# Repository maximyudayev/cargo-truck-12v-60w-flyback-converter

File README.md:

# Heavy-Duty Truck 12V 60W Flyback DC/DC Converter
18V-32V input 12V output, 60W (5A) nominal 84W (7A) maximum, 60mm-by-30mm-by-25mm, no-opto flyback DC/DC converter with synchronous secondary rectifier, up to 97% efficiency, excellent static and dynamic output regulation for heavy-duty truck applications like interior appliances, ADAS, lighting, supplies for consumer electronics, etc.

Below is the efficiency and duty cycle graph as a function of load:

This DC/DC converter was built as part of my Power Electronics course at KU Leuven - Campus GroupT in academic year 2020-2021, taught by the awesome duo of Gert and Gorik :wink:

The converter was designed, built and tested. Results of the test can be found in the final report of the course, which also includes all the detailed calculation steps and side-by-side comparison to a synchronous buck converter designed and built by my lab partner Matthias.

## Features
- [X] Clean, readable and well-documented
- [X] Operating range of normal battery voltages
- [X] <500mV input/output ripple
- [X] Low-cost prototype
- [X] Dual-variant primary clamp
- [X] Dual-variant secondary rectifier
- [ ] TVS circuit on the input
- [ ] Multiple output rails (5V, 3V3)
- [ ] Dynamic load ripple under 50-100mV
- [ ] Heat management #1

PCB front side:

PCB back side:

All the design files are under GPL3 and can be freely used for personal projects where this device can be of use.

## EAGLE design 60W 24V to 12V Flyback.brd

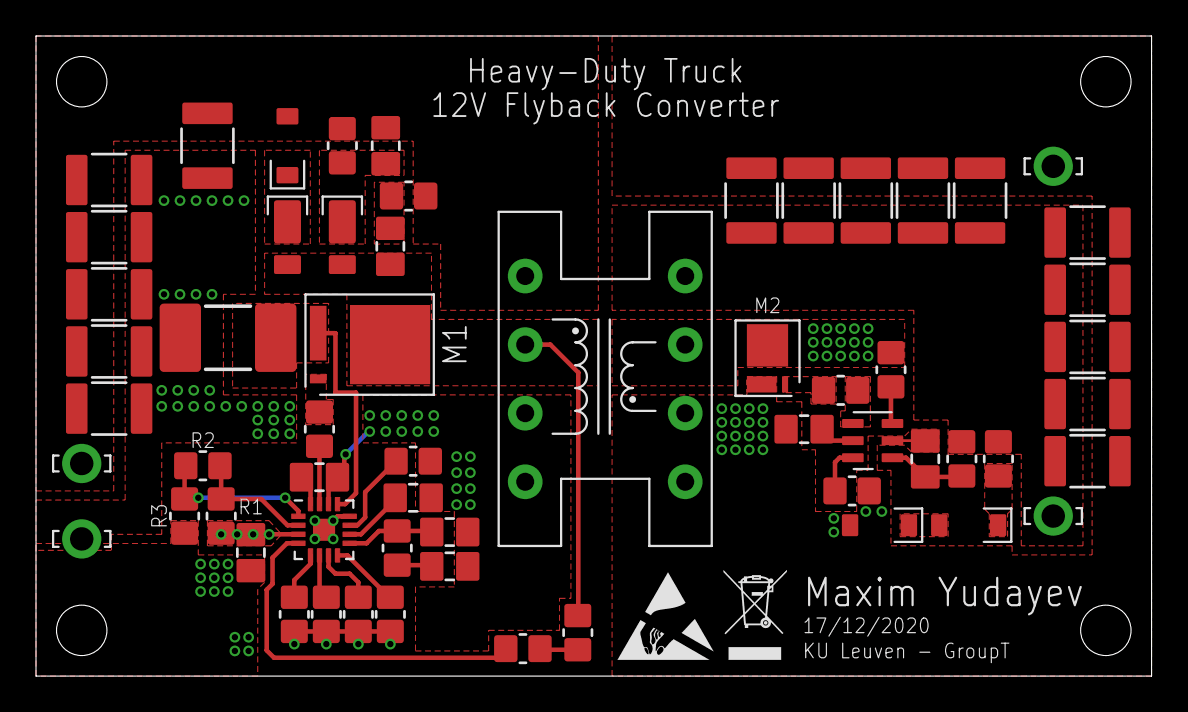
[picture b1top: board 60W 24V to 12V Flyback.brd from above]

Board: 2 copper layers, 62.0 x 35.6 mm, 60 parts (1 on the bottom side), 33 nets.

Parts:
+12V, +24V: TAB_37800568(MSTIN); HOLE_1-3
C1, C2, C3, C4, C5, C6, C7, C8, C9, C10: 22u; C1210K
C11, C12, C13, C14, C15, C16: 10u; C1210K
C17, C18, C19, C23: 4u7; C0805K
C20, C22: 47n; C0805K
C21: 560p; C0805K
C24: 220p; C0805K
C25: 150n; C0805K
CHASSIS: TAB_37800568(MSTIN); HOLE_1-3
D1, D3: DFLS2100-7; DFLS2100_DS31475
D2: MMSZ5270BT1G; MMSZ?T1G_SOD-123_425-04
D4, D5: MMSZ4692T1G; MMSZ?T1G_SOD-123_425-04
D6: B540C-13-F; B5?0C-13-F_DO-214AB_DS13012
GND: TAB_37800568(MSTIN); HOLE_1-3
M1: BSC096N10LS5; BSC096N10LS5_TDSON-8
M2: BSZ039N06NS; BSZ039N06NS_TSDSON-8_Z8B00158553
R1: 228k; R0805
R2: 3k83; R0805
R3, R4: 10k; R0805
R5: 6k49; R0805
R6: 22; R0805
R7: 147k; R0805
R8: 5m; R2512
R9: 3k6; R0805
R10: 33k2; R0805
R11: 137k; R0805
R12: 124k; R0805
R13: R0805
R14: 357; R0805
R15, R16: 1R2; R0805
R17: 220k; R0805
R18: 47; R0805
R19: 10k2; R0805
R20: 5R1; R0805
T1: TRANS_EPCOS_8; TRANS_EPCOS-B66307_E16/8/5_0.5_3.45UH_200K
U1: MAX17960; T1633-4
U2: MAX17606; MAX17606_90-0242

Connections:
+12V: +12V.P$1, C1.1, C2.1, C3.1, C4.1, C5.1, C6.1, C7.1, C8.1, C9.1, C10.1, R6.2, R20.2, T1.8
+24V: +24V.P$1, C11.1, C12.1, C13.1, C14.1, C15.1, C16.1, C23.1, C25.1, D2.A, R1.2, R18.2, R19.2, T1.1, U1.VIN
EN/UVLO: R1.1, R2.2, U1.EN/UVLO
GND: C11.2, C12.2, C13.2, C14.2, C15.2, C16.2, C19.2, C20.2, C21.2, C22.2, C23.2, CHASSIS.P$1, R3.1, R4.2, R8.1, R10.1, R11.1, R12.1, R13.1, U1.EP, U1.PGND, U1.SGND
GND5: C1.2, C2.2, C3.2, C4.2, C5.2, C6.2, C7.2, C8.2, C9.2, C10.2, C17.2, C18.2, D5.A, D6.A, GND.P$1, M2.S, R7.1, U2.GND
unnamed: R4.1, U1.SET
unnamed: C18.1, U2.VDRV
unnamed: R17.1, U1.FB
unnamed: C24.1, R18.1
unnamed: C17.1, R6.1, U2.VIN
unnamed: R7.2, U2.TOFF
unnamed: R14.2, U2.DRN
unnamed: C19.1, U1.INTVCC
unnamed: C25.2, D1.C, R19.1
unnamed: C20.1, R9.1
unnamed: C21.1, R9.2, U1.COMP
unnamed: R10.2, U1.RT
unnamed: C22.1, U1.SS
unnamed: R12.2, U1.VCM
unnamed: R11.2, U1.RIN
unnamed: R13.2, U1.TC
unnamed: R15.1, U1.NDRV
unnamed: R16.2, U2.GATE
unnamed: R5.1, R17.2
unnamed: D2.C, D3.C
unnamed: D4.C, R20.1
unnamed: D4.A, D5.C
OVI: R2.1, R3.2, U1.OVI
PRI_MOS_D: C24.2, D1.A, D3.A, M1.D, R5.2, T1.2
PRI_MOS_G: M1.G, R15.2
PRI_MOS_S: M1.S, R8.2, U1.CS
SEC_MOS_D: D6.C, M2.D, R14.1, T1.7
SEC_MOS_G: M2.G, R16.1

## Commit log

2021-02-07 Uploaded all design files.
    +: Schematic and board layout
    +: BMP files
    +: Front and back renderings
    +: Schematic screenshots
    +: Bill of materials
    +: .gitignore
2021-02-07 Elaborated in README.
2021-02-07 Uploaded report.
